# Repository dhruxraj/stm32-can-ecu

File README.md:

# STM32 CAN ECU – development board (rev A)

A compact, "ECU-style" CAN node for learning and prototyping automotive-type embedded software. It has an STM32G4 MCU, a CAN transceiver with protection and switchable termination, a 6-axis IMU, a protected 8-18 V supply, SWD, a UART, LEDs and buttons.

Two or more identical boards talk to each other over CANH/CANL/GND. Each board broadcasts:

* a heartbeat,
* IMU data,
* supply voltage,
* diagnostics.

Each board also supervises its peers.

## Quick facts

| | |
|---|---|
| MCU | **STM32G431CBT6** (Cortex-M4F 170 MHz, 128 KB flash, 32 KB RAM, LQFP48) |
| CAN transceiver | **NXP TJA1051T/3** (5 V VCC, 3.3 V VIO), PESD1CAN ESD, split termination on jumper |
| IMU | **ST LSM6DS3TR-C** (accel ±4 g, gyro ±500 dps, I2C 0x6A) |
| Supply | **8-18 V DC** (12 V nominal): PTC + TVS + reverse-polarity diode → RECOM R-78E5.0-0.5 (5 V) → AP2112K-3.3 LDO |
| Power | ≈ 0.35 W typical, < 0.85 W worst case (≈ 28 mA typical / 67 mA worst case at 12 V) |
| PCB | **80 × 60 mm, 4 layers** (signal / GND / 3V3 / signal), 1.6 mm, 4 × M3 |
| CAN | classic CAN 500 kbit/s, 11-bit IDs, counter + CRC-8 on every frame |
| Est. BOM cost | ≈ USD 19 components per board (qty 10, rough estimate) + PCB |
| Tools | KiCad 7/8/9, STM32CubeIDE or CMake + arm-none-eabi-gcc, ST-LINK |

## Repository layout

```
README.md                  this file
docs/                      all documentation (start with BRINGUP.md when your boards arrive)
hardware/kicad/            KiCad project: CAN_ECU.kicad_pro / .kicad_sch / .kicad_pcb + libraries
hardware/fab/              preview Gerbers, drill files, BOM.csv, CPL_top.csv
hardware/gen/              Python generators + independent checkers (how rev A was produced)
firmware/                  STM32Cube HAL firmware (CMake / CubeIDE), host unit tests
tools/                     can_ecu.dbc, Python decoder/monitor (python-can)
```

## Architecture

| Document | Content |
|---|---|
| [docs/DESIGN_NOTES.md](docs/DESIGN_NOTES.md) | architecture, all design decisions, circuit calculations, **assumptions list**, limitations, future work |
| [docs/POWER_CALCS.md](docs/POWER_CALCS.md) | per-rail current budget, regulator dissipation, input current, total power |
| [docs/PIN_MAPPING.md](docs/PIN_MAPPING.md) | all 48 MCU pins, alternate functions, connector and jumper pinouts |
| [docs/COMPONENTS.md](docs/COMPONENTS.md) | component list and footprint list (with **VERIFY** notes) |
| [docs/PCB_LAYOUT.md](docs/PCB_LAYOUT.md) | stack-up, rules, placement and routing strategy |
| [docs/CAN_PROTOCOL.md](docs/CAN_PROTOCOL.md) | IDs, byte layouts, scaling, rates, status bits, counter/CRC, fault bits |
| [docs/FIRMWARE.md](docs/FIRMWARE.md) | module structure, scheduler, robustness features, building, programming |
| [docs/MANUFACTURING.md](docs/MANUFACTURING.md) | fab spec, how to produce/order Gerbers, assembly notes, cost |
| [docs/BRINGUP.md](docs/BRINGUP.md) | step-by-step bring-up, **two-board CAN test**, troubleshooting |
| [docs/TEST_CHECKLIST.md](docs/TEST_CHECKLIST.md) | per-board test sheet |
| [docs/VALIDATION_REPORT.md](docs/VALIDATION_REPORT.md) | results of all automated checks and what could not be checked |

## Hardware overview

* **Power input.** J1 (5.08 mm screw terminal) → F1 PTC 0.5 A → D1 SMBJ18A TVS → D2 SS34 series Schottky → 10 µF + 47 µF → R-78E 5 V module → AP2112K 3.3 V LDO. The MCU's analog supply (VDDA/VREF+) is filtered by FB1. The PWR LED is on +5 V. VIN is measured by the MCU (PA0).
* **MCU.** STM32G431CBT6 with an 8 MHz crystal (PLL 170 MHz) and 100 nF per VDD pin plus 4.7 µF bulk. It has a reset button and SWD header, BOOT0 pull-down plus jumper, and two node-ID jumpers. Unused pins are left unconnected and set to analog.
* **CAN.** FDCAN1 (PA11/PA12) → TJA1051T/3 → PESD1CAN → J2/J3 (1 CANH, 2 CANL, 3 GND, paralleled). JP2 enables the 2 × 60.4 Ω split termination with 4.7 nF to GND. The transceiver's S pin holds it silent until the firmware is ready. Test pads: TP1 CANH, TP2 CANL, TP7 CAN_TX, TP8 CAN_RX.
* **IMU.** LSM6DS3TR-C on I2C1 (PA15/PB7, 4k7 pull-ups), with INT1/INT2 wired to PB5/PB9.
* **User interface.** LEDs STATUS/FAULT/CAN-TX/CAN-RX plus PWR; RESET and USER buttons; J5 2×5 header (3.3 V UART + 5 GPIO/ADC).

## Software overview

* **Firmware.** Bare-metal C using the STM32Cube HAL. A cooperative scheduler runs 10/20/100/1000 ms tasks.
* **CAN.** Interrupt-driven FDCAN RX into a ring buffer, with hardware ID filters and automatic bus-off recovery.
* **Protocol.** IMU data at 50 Hz, heartbeat and board data at 10 Hz, diagnostics at 1 Hz. Every frame carries a rolling counter and a CRC-8.
* **Supervision.** Peer heartbeat timeout of 300 ms. Node states are INIT/RUN/DEGRADED/FAULT, with 13 fault bits (active + latched).
* **Robustness.** Independent watchdog (~1 s), reset-cause reporting, crystal-failure fallback, IMU fault detection with auto re-init.
* **PC side.** `tools/can_monitor.py` (python-can) decodes and verifies all frames and can send commands. `tools/can_ecu.dbc` works in any CAN analyzer.

## Getting started

### 1. Open the design in KiCad

1. Install KiCad 7, 8 or 9.
2. Copy/unzip the project and open **`hardware/kicad/CAN_ECU.kicad_pro`**.
   * Symbols and footprints come from the project-local libraries `CAN_ECU.kicad_sym` / `CAN_ECU.pretty`. They are registered in the project's `sym-lib-table` / `fp-lib-table`, so no library setup is needed.
   * KiCad 8/9 will say the files were made by an older version. Accept; saving converts them.
3. **Schematic:** open the schematic editor and run **Inspect → Electrical Rules Checker**.
4. **PCB:**
   1. Open the PCB editor and press **B** (Fill All Zones). The planes and pours are stored unfilled.
   2. Run **Inspect → Design Rules Checker**. Enable "Test for parity between PCB and schematic".
   3. Use **View → 3D Viewer** for a sanity check. 3D models are not linked, so only footprint outlines appear.

### 2. Order boards

See [docs/MANUFACTURING.md](docs/MANUFACTURING.md). In short:

1. Fill the zones, run DRC and plot Gerbers + drill files from KiCad.
2. Order a 4-layer, 1.6 mm board with ENIG finish.
3. Buy the parts from `hardware/fab/BOM.csv`. Verify the footprints marked **VERIFY** in docs/COMPONENTS.md first.

### 3. Build and flash the firmware

```bash
cd firmware && ./scripts/fetch_st_drivers.sh
cmake -B build -DCMAKE_TOOLCHAIN_FILE=cmake/gcc-arm-none-eabi.cmake && cmake --build build
STM32_Programmer_CLI -c port=SWD mode=UR -w build/can_ecu.hex -v -rst
```

Connect the ST-LINK to J4:

| J4 pin | Signal |
|---|---|
| 1 | VDD (sense) |
| 2 | SWCLK |
| 3 | GND |
| 4 | SWDIO |
| 5 | NRST |
| 6 | SWO |

The board must be powered from J1 while you program it. For the console, use a 3.3 V USB-UART on J5 (pin 3 TX, pin 4 RX, pin 2 GND) at 115200 8N1. CubeIDE instructions are in [docs/FIRMWARE.md](docs/FIRMWARE.md).

### 4. Connect two boards and test CAN

1. Board A: JP3 and JP4 open (**node 0**). Board B: **JP3 closed (node 1)**.
2. On a 2-node bus both boards are bus ends, so **fit both JP2 shunts (1-3 and 2-4) on both boards**. With power off, CANH-CANL must measure ≈ 60 Ω.
3. Wire J2/J3 pin 1-1 (CANH), 2-2 (CANL), 3-3 (GND), using a twisted pair for CANH/CANL.
4. Power both boards (8-18 V).
5. Check the result:
   * Both STATUS LEDs flash at 1 Hz (RUN) and the CAN-TX/RX LEDs flicker.
   * Each UART prints `peer node X online`, and the status line shows the peer's accelerometer values.
   * Pressing USER on one board makes the other blink fast for 3 s.
   * Unplugging the cable gives `PEER_TIMEOUT` (DEGRADED) within 300 ms; the boards recover automatically when you plug it back in.
6. With a USB-CAN adapter, run `python3 tools/can_monitor.py -i socketcan -c can0`. Expect about 121 frames/s per node with zero CRC or counter errors.

The full procedure, expected values and scope checks are in [docs/BRINGUP.md](docs/BRINGUP.md).

## Troubleshooting (short)

| Symptom | Check |
|---|---|
| One board alone shows DEGRADED + `CAN_PASSIVE` | Normal: CAN needs a second node to acknowledge frames. |
| Two boards don't see each other | Node IDs must differ. Check CANH↔CANH / CANL↔CANL wiring, the GND wire, and that termination measures ≈ 60 Ω. |
| `HSI16 FALLBACK` printed | Crystal not starting: check the joints and C16/C17. |
| `IMU_COMM` fault / WHO_AM_I 0x00 | IMU (LGA) soldering, or pull-ups R13/R14. |
| No +3V3 | U2 orientation; a short on +3V3. |
| ST-LINK can't connect | Use "connect under reset"; make sure JP1 (BOOT0) is open. |

More in [docs/BRINGUP.md](docs/BRINGUP.md#5-troubleshooting).

## Validation status (honest summary)

* **PCB design-rule check** (independent checker, 0.2 mm rules): **0 violations, 0 unconnected nets**. Both planes are continuous, and there are no courtyard overlaps.
* **Generated KiCad files re-parsed:**
  * S-expression syntax is valid.
  * The schematic netlist equals the PCB netlist for all 46 nets.
  * The ERC subset passes, and there are no silkscreen collisions.
* **Firmware:** 60 host unit checks pass (protocol, diagnostics, IMU conversion). All sources compile cleanly against a HAL stub, and the Python decoder matches the C golden frames.
* **Not verified here:**
  * KiCad's own ERC/DRC and zone fill (KiCad was not available).
  * A real arm-none-eabi build against the ST HAL.
  * Operation on hardware.
  * Footprints marked VERIFY.

  Details and remaining risks are in [docs/VALIDATION_REPORT.md](docs/VALIDATION_REPORT.md) and [docs/DESIGN_NOTES.md](docs/DESIGN_NOTES.md#4-assumptions-and-items-that-were-not-fully-verified).

## Limitations

This is a development board, **not an automotive-qualified ECU**:

* No ISO 7637 / ISO 16750 load-dump protection.
* No CAN common-mode choke.
* No USB in rev A: it conflicts with the CAN pins on this MCU.
* A single CAN channel.
* The counter/CRC/state machine is AUTOSAR-*inspired*, not compliant.

See [docs/DESIGN_NOTES.md](docs/DESIGN_NOTES.md#5-limitations-of-rev-a).

## Future improvements

* A 2-FDCAN MCU with USB-C.
* A discrete wide-input buck with ideal-diode reverse protection and load-dump rating.
* CAN FD, and a CAN bootloader.
* A CMC footprint.
* UDS-style diagnostics.

See [docs/DESIGN_NOTES.md](docs/DESIGN_NOTES.md#6-future-improvements).

## License

This project uses separate licenses for hardware, software, and documentation.

- **Hardware:** CERN-OHL-P-2.0
- **Firmware and software tools:** MIT License
- **Documentation:** CC BY 4.0

See the corresponding `LICENSE-*` files in the repository for the
complete license terms.

Third-party components retain their original licenses.

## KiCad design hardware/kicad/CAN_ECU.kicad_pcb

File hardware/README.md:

# Hardware

```
hardware/
  kicad/     KiCad project (open CAN_ECU.kicad_pro) + project symbol/footprint libraries
  fab/       preview Gerbers, drill files, BOM.csv, CPL_top.csv (regenerate from KiCad for ordering)
  gen/       Python generators - the design "source code"
```

`gen/` is how every hardware file in this project was produced. KiCad itself was not available while the files were generated, so they were written by these scripts.

| Script | Purpose |
|---|---|
| `design.py` | parts, values, part numbers and the pin→net netlist (single source of truth) |
| `lib.py` | symbol and footprint definitions |
| `board.py` | board outline and component placement |
| `routing.py` | hand routes, plane fan-out and a constrained router for the low-speed nets |
| `write_kicad.py` | writes the `.kicad_sch/.kicad_pcb/.kicad_pro/.kicad_sym/.pretty` files |
| `checks.py` | independent DRC, connectivity and plane-continuity checks |
| `validate_files.py` | re-parses the written files: syntax, schematic↔PCB netlist, ERC subset, silkscreen |
| `fab.py` | Gerber/Excellon/BOM/CPL + Gerber re-render |
| `gen_docs.py` | pin map, component list, validation report, figures |

Regenerate everything (Python 3.10+, numpy, scipy, matplotlib): `cd hardware/gen && ./build_all.sh`

**Recommended workflow once you own the design:** open the project in KiCad and continue there. KiCad becomes the source of truth from that point, and the generators are then only a record of how rev A was made. Do not mix the two workflows: re-running the generators overwrites manual KiCad edits.

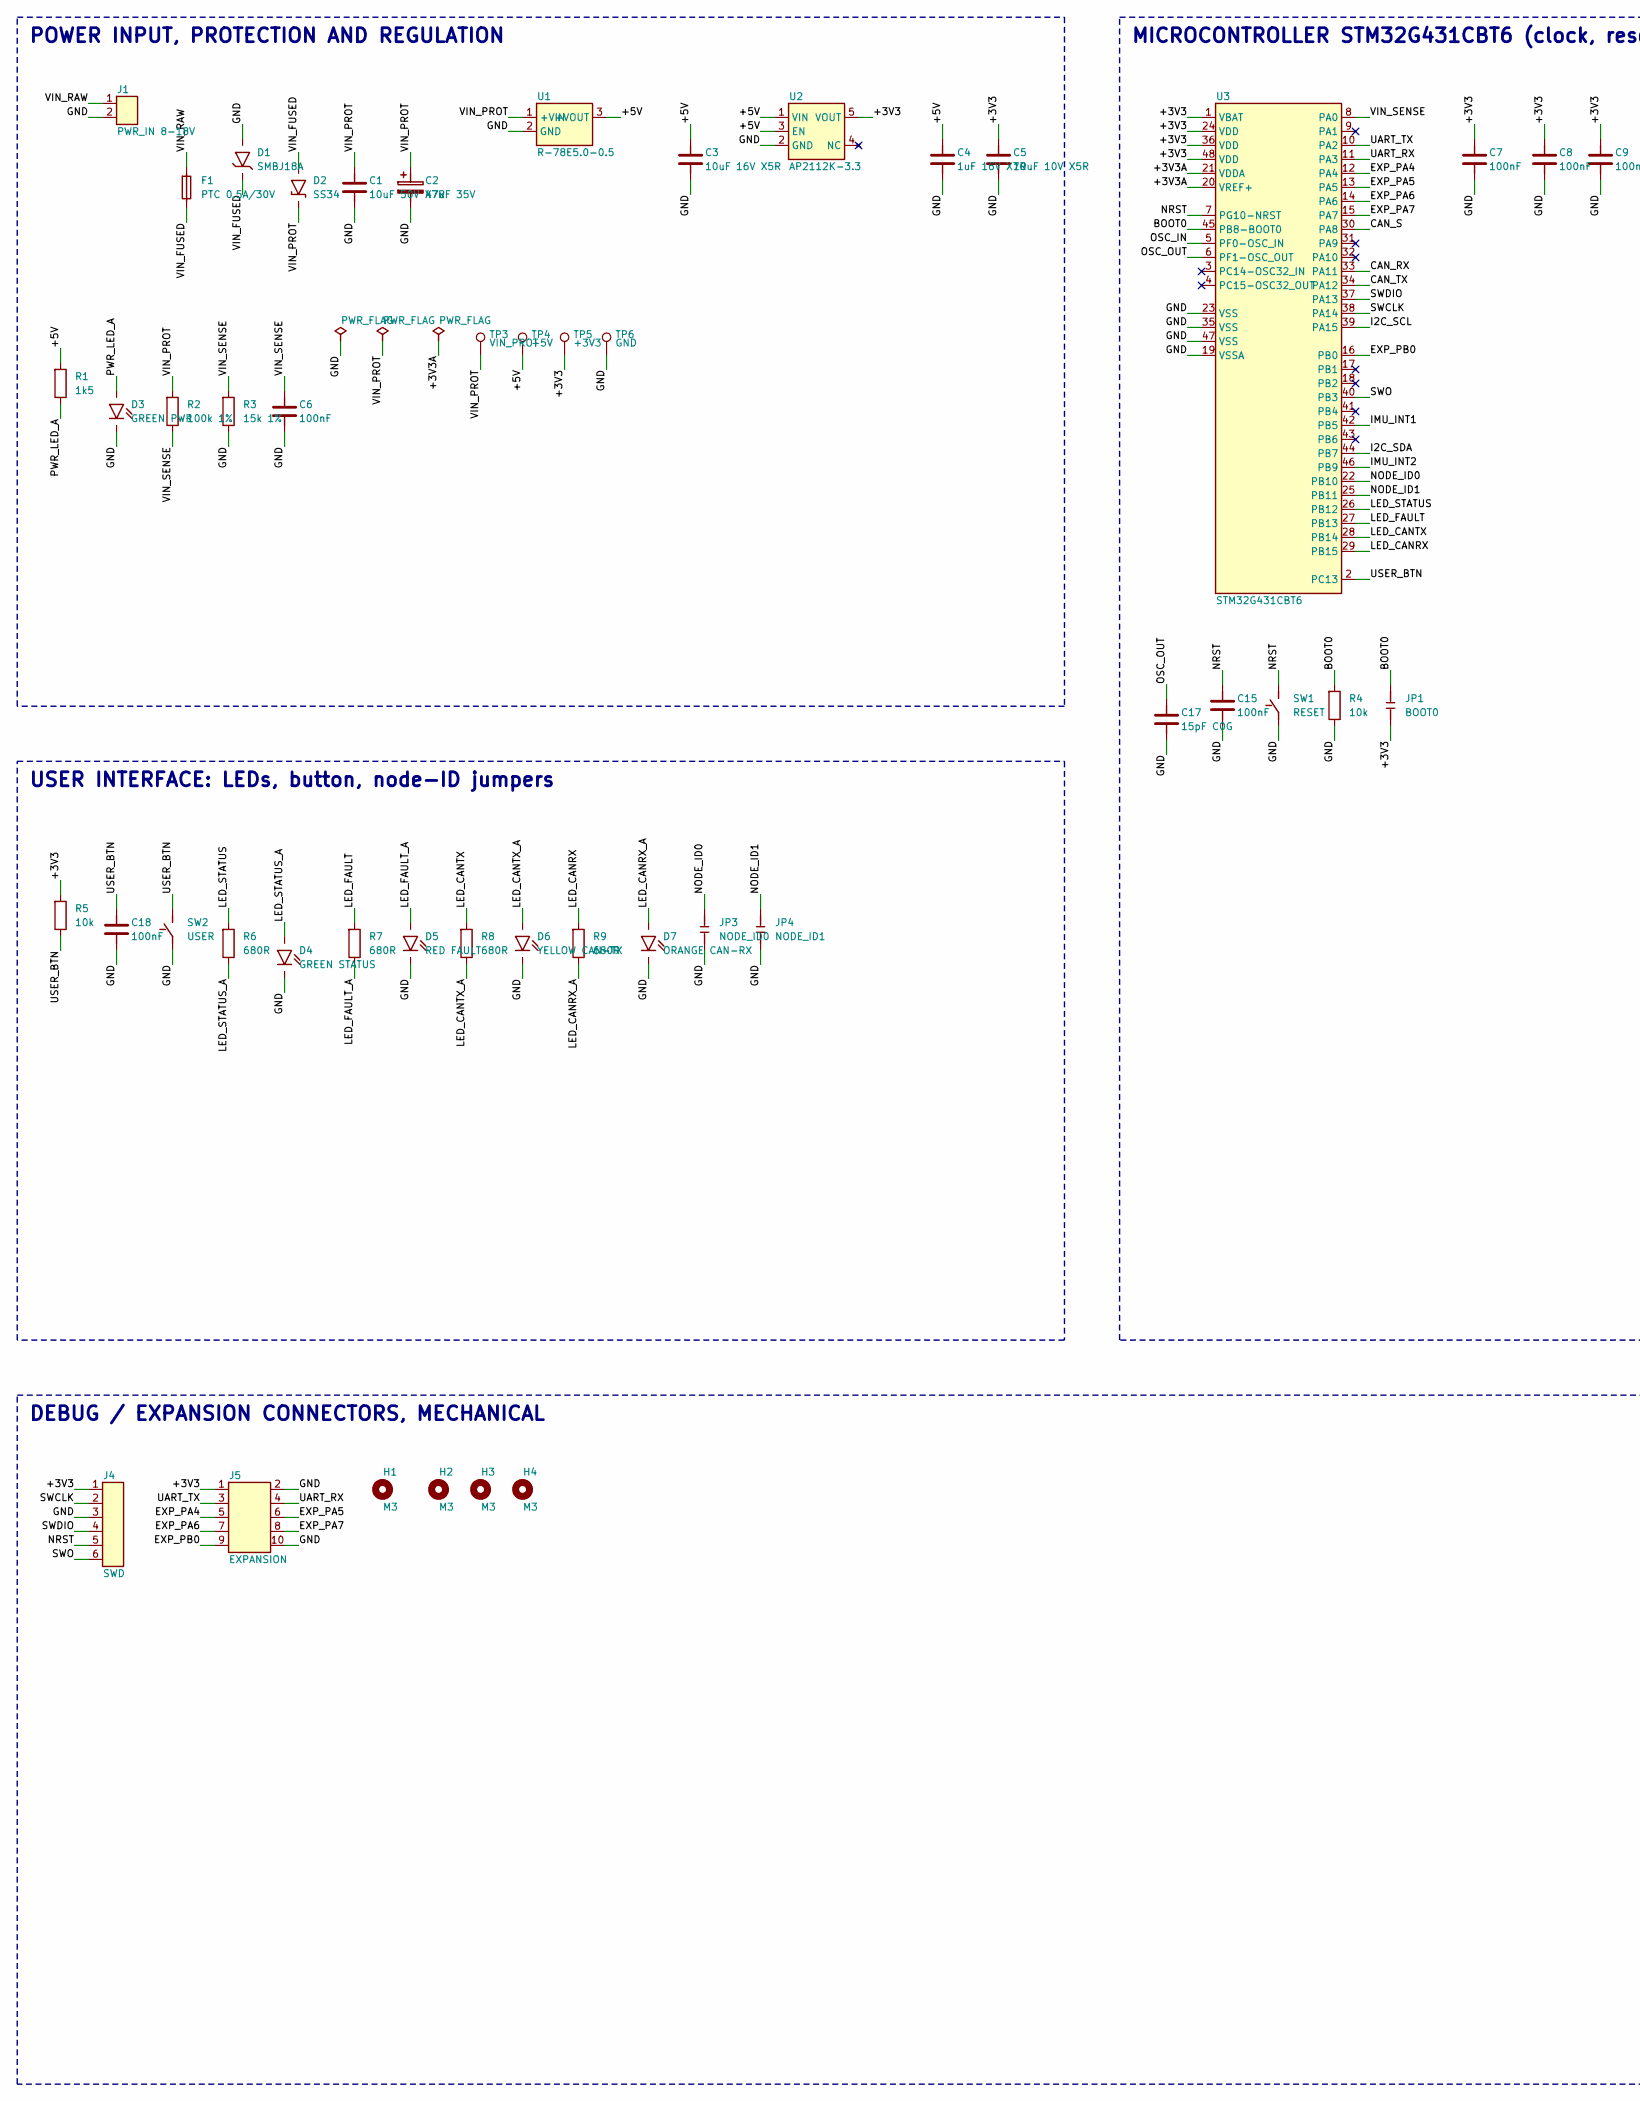
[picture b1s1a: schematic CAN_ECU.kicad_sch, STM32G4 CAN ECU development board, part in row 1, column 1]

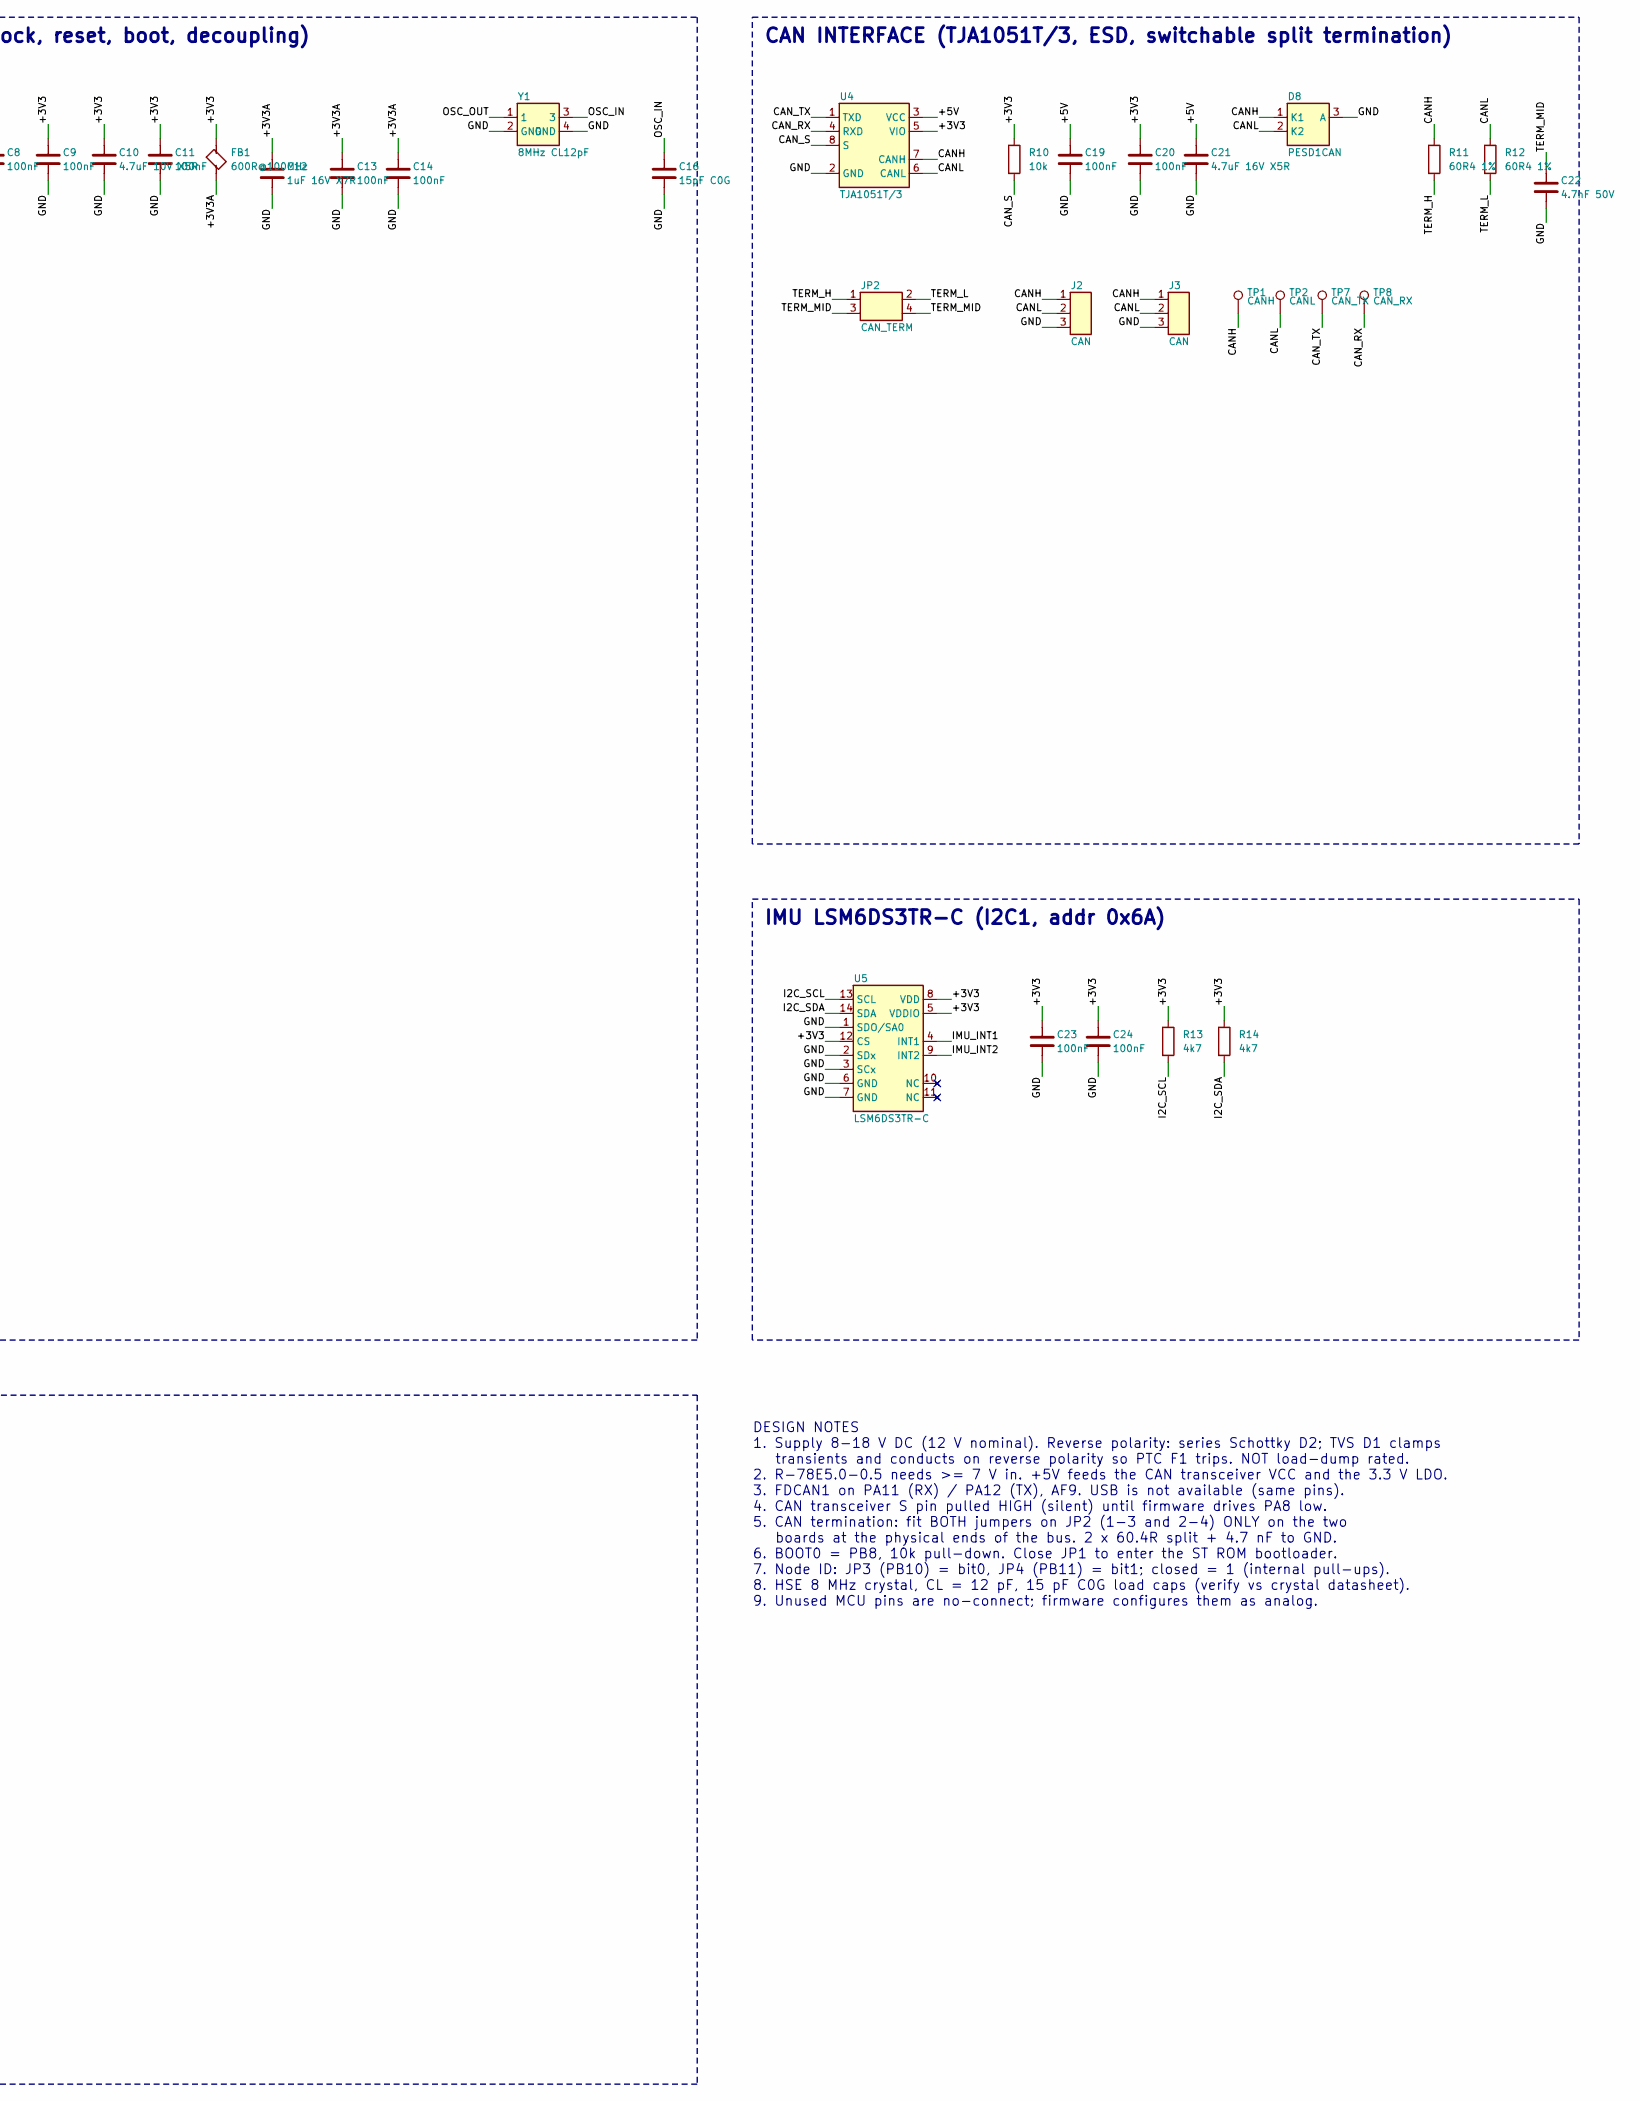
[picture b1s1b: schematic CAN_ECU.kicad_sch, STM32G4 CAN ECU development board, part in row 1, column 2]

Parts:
C1: 10uF 50V X7R; C_1210_3225Metric
C2: 47uF 35V; CP_Radial_D6.3mm_P2.50mm; MPN 47 uF 35 V aluminium electrolytic, D6.3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
C3: 10uF 16V X5R; C_0805_2012Metric
C4, C12: 1uF 16V X7R; C_0603_1608Metric
C5: 10uF 10V X5R; C_0805_2012Metric
C6, C7, C8, C9, C11, C13, C14, C15, C18, C19, C20, C23, C24: 100nF; C_0603_1608Metric
C10: 4.7uF 10V X5R; C_0805_2012Metric
C16, C17: 15pF C0G; C_0603_1608Metric
C21: 4.7uF 16V X5R; C_0805_2012Metric
C22: 4.7nF 50V; C_0603_1608Metric
D1: SMBJ18A; D_SMB; MPN SMBJ18A
D2: SS34; D_SMA; MPN SS34
D3: GREEN PWR; LED_0603_1608Metric; MPN 0603 green LED, Vf~2.0 V
D4: GREEN STATUS; LED_0603_1608Metric; MPN 0603 green LED
D5: RED FAULT; LED_0603_1608Metric; MPN 0603 red LED
D6: YELLOW CAN-TX; LED_0603_1608Metric; MPN 0603 yellow LED
D7: ORANGE CAN-RX; LED_0603_1608Metric; MPN 0603 orange LED
D8: PESD1CAN; SOT-23; MPN PESD1CAN,215
F1: PTC 0.5A/30V; Fuse_1812_4532Metric; MPN 1812 PTC, Ihold 0.5 A, Vmax >= 30 V (e.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
FB1: 600R@100MHz; L_0603_1608Metric; MPN BLM18AG601SN1D (or equiv. 0603 bead, >=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
H1, H2, H3, H4: M3; MountingHole_3.2mm_M3
J1: PWR_IN 8-18V; TerminalBlock_1x02_P5.08mm_Horizontal; MPN 1729128 (MKDS 1,5/ 2-5,08) or equivalent
J2, J3: CAN; TerminalBlock_1x03_P5.08mm_Horizontal; MPN 1729131 (MKDS 1,5/ 3-5,08) or equivalent
J4: SWD; PinHeader_1x06_P2.54mm_Vertical; MPN 1x6 2.54 mm pin header
J5: EXPANSION; PinHeader_2x05_P2.54mm_Vertical; MPN 2x5 2.54 mm pin header
JP1: BOOT0; SolderJumper-2_P1.3mm_Open_Pad1.0x1.5mm
JP2: CAN_TERM; PinHeader_2x02_P2.54mm_Vertical; MPN 2x2 2.54 mm header + 2 jumper shunts
JP3: NODE_ID0; SolderJumper-2_P1.3mm_Open_Pad1.0x1.5mm
JP4: NODE_ID1; SolderJumper-2_P1.3mm_Open_Pad1.0x1.5mm
R1: 1k5; R_0603_1608Metric
R2: 100k 1%; R_0603_1608Metric
R3: 15k 1%; R_0603_1608Metric
R4, R5, R10: 10k; R_0603_1608Metric
R6, R7, R8, R9: 680R; R_0603_1608Metric
R11, R12: 60R4 1%; R_0805_2012Metric
R13, R14: 4k7; R_0603_1608Metric
SW1: RESET; SW_PUSH_6mm; MPN 6x6 mm THT tactile switch
SW2: USER; SW_PUSH_6mm; MPN 6x6 mm THT tactile switch
TP1: CANH; TestPoint_Pad_D1.5mm
TP2: CANL; TestPoint_Pad_D1.5mm
TP3: VIN_PROT; TestPoint_Pad_D1.5mm
TP4: +5V; TestPoint_Pad_D1.5mm
TP5: +3V3; TestPoint_Pad_D1.5mm
TP6: GND; TestPoint_Pad_D1.5mm
TP7: CAN_TX; TestPoint_Pad_D1.5mm
TP8: CAN_RX; TestPoint_Pad_D1.5mm
U1: R-78E5.0-0.5; Converter_DCDC_RECOM_R-78E-0.5_THT; MPN R-78E5.0-0.5
U2: AP2112K-3.3; SOT-23-5; MPN AP2112K-3.3TRG1
U3: STM32G431CBT6; LQFP-48_7x7mm_P0.5mm; MPN STM32G431CBT6
U4: TJA1051T/3; SOIC-8_3.9x4.9mm_P1.27mm; MPN TJA1051T/3,118
U5: LSM6DS3TR-C; LGA-14_3x2.5mm_P0.5mm_LayoutBorder3x4y; MPN LSM6DS3TR-C
Y1: 8MHz CL12pF; Crystal_SMD_3225-4Pin_3.2x2.5mm; MPN 8.000 MHz, 3225 4-pad, +-20 ppm, CL = 1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

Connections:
+3V3: C5.1, C7.1, C8.1, C9.1, C10.1, C11.1, C20.1, C23.1, C24.1, FB1.1, J4.1, J5.1, JP1.2, R5.1, R10.1, R13.1, R14.1, TP5.1, U2.5 (VOUT), U3.1 (VBAT), U3.24 (VDD), U3.36 (VDD), U3.48 (VDD), U4.5 (VIO), U5.5 (VDDIO), U5.8 (VDD), U5.12 (CS)
+3V3A: C12.1, C13.1, C14.1, FB1.2, U3.20 (VREF+), U3.21 (VDDA)
+5V: C3.1, C4.1, C19.1, C21.1, R1.1, TP4.1, U1.3 (+VOUT), U2.1 (VIN), U2.3 (EN), U4.3 (VCC)
BOOT0: JP1.1, R4.1, U3.45 (PB8-BOOT0)
CANH: D8.1 (K1), J2.1, J3.1, R11.1, TP1.1, U4.7 (CANH)
CANL: D8.2 (K2), J2.2, J3.2, R12.1, TP2.1, U4.6 (CANL)
CAN_RX: TP8.1, U3.33 (PA11), U4.4 (RXD)
CAN_S: R10.2, U3.30 (PA8), U4.8 (S)
CAN_TX: TP7.1, U3.34 (PA12), U4.1 (TXD)
EXP_PA4: J5.5, U3.12 (PA4)
EXP_PA5: J5.6, U3.13 (PA5)
EXP_PA6: J5.7, U3.14 (PA6)
EXP_PA7: J5.8, U3.15 (PA7)
EXP_PB0: J5.9, U3.16 (PB0)
GND: C1.2, C2.2, C3.2, C4.2, C5.2, C6.2, C7.2, C8.2, C9.2, C10.2, C11.2, C12.2, C13.2, C14.2, C15.2, C16.2, C17.2, C18.2, C19.2, C20.2, C21.2, C22.2, C23.2, C24.2, D1.2 (A), D3.1 (K), D4.1 (K), D5.1 (K), D6.1 (K), D7.1 (K), D8.3 (A), J1.2, J2.3, J3.3, J4.3, J5.2, J5.10, JP3.2, JP4.2, R3.2, R4.2, SW1.2, SW2.2, TP6.1, U1.2 (GND), U2.2 (GND), U3.19 (VSSA), U3.23 (VSS), U3.35 (VSS), U3.47 (VSS), U4.2 (GND), U5.1 (SDO/SA0), U5.2 (SDx), U5.3 (SCx), U5.6 (GND), U5.7 (GND), Y1.2 (GND), Y1.4 (GND)
I2C_SCL: R13.2, U3.39 (PA15), U5.13 (SCL)
I2C_SDA: R14.2, U3.44 (PB7), U5.14 (SDA)
IMU_INT1: U3.42 (PB5), U5.4 (INT1)
IMU_INT2: U3.46 (PB9), U5.9 (INT2)
LED_CANRX: R9.1, U3.29 (PB15)
LED_CANRX_A: D7.2 (A), R9.2
LED_CANTX: R8.1, U3.28 (PB14)
LED_CANTX_A: D6.2 (A), R8.2
LED_FAULT: R7.1, U3.27 (PB13)
LED_FAULT_A: D5.2 (A), R7.2
LED_STATUS: R6.1, U3.26 (PB12)
LED_STATUS_A: D4.2 (A), R6.2
NODE_ID0: JP3.1, U3.22 (PB10)
NODE_ID1: JP4.1, U3.25 (PB11)
NRST: C15.1, J4.5, SW1.1, U3.7 (PG10-NRST)
OSC_IN: C16.1, U3.5 (PF0-OSC_IN), Y1.3
OSC_OUT: C17.1, U3.6 (PF1-OSC_OUT), Y1.1
PWR_LED_A: D3.2 (A), R1.2
SWCLK: J4.2, U3.38 (PA14)
SWDIO: J4.4, U3.37 (PA13)
SWO: J4.6, U3.40 (PB3)
TERM_H: JP2.1, R11.2
TERM_L: JP2.2, R12.2
TERM_MID: C22.1, JP2.3, JP2.4
UART_RX: J5.4, U3.11 (PA3)
UART_TX: J5.3, U3.10 (PA2)
USER_BTN: C18.1, R5.2, SW2.1, U3.2 (PC13)
VIN_FUSED: D1.1 (K), D2.2 (A), F1.2
VIN_PROT: C1.1, C2.1, D2.1 (K), R2.1, TP3.1, U1.1 (+VIN)
VIN_RAW: F1.1, J1.1
VIN_SENSE: C6.1, R2.2, R3.1, U3.8 (PA0)

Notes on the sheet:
POWER INPUT, PROTECTION AND REGULATION
MICROCONTROLLER STM32G431CBT6 (clock, reset, boot, decoupling)
CAN INTERFACE (TJA1051T/3, ESD, switchable split termination)
IMU LSM6DS3TR-C (I2C1, addr 0x6A)
USER INTERFACE: LEDs, button, node-ID jumpers
DEBUG / EXPANSION CONNECTORS, MECHANICAL
DESIGN NOTES 1. Supply 8-18 V DC (12 V nominal). Reverse polarity: series Schottky D2; TVS D1 clamps transients and conducts on reverse polarity so PTC F1 trips. NOT load-dump rated. 2. R-78E5.0-0.5 needs >= 7 V in. +5V feeds the CAN transceiver VCC and the 3.3 V LDO. 3. FDCAN1 on PA11 (RX) / PA12 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

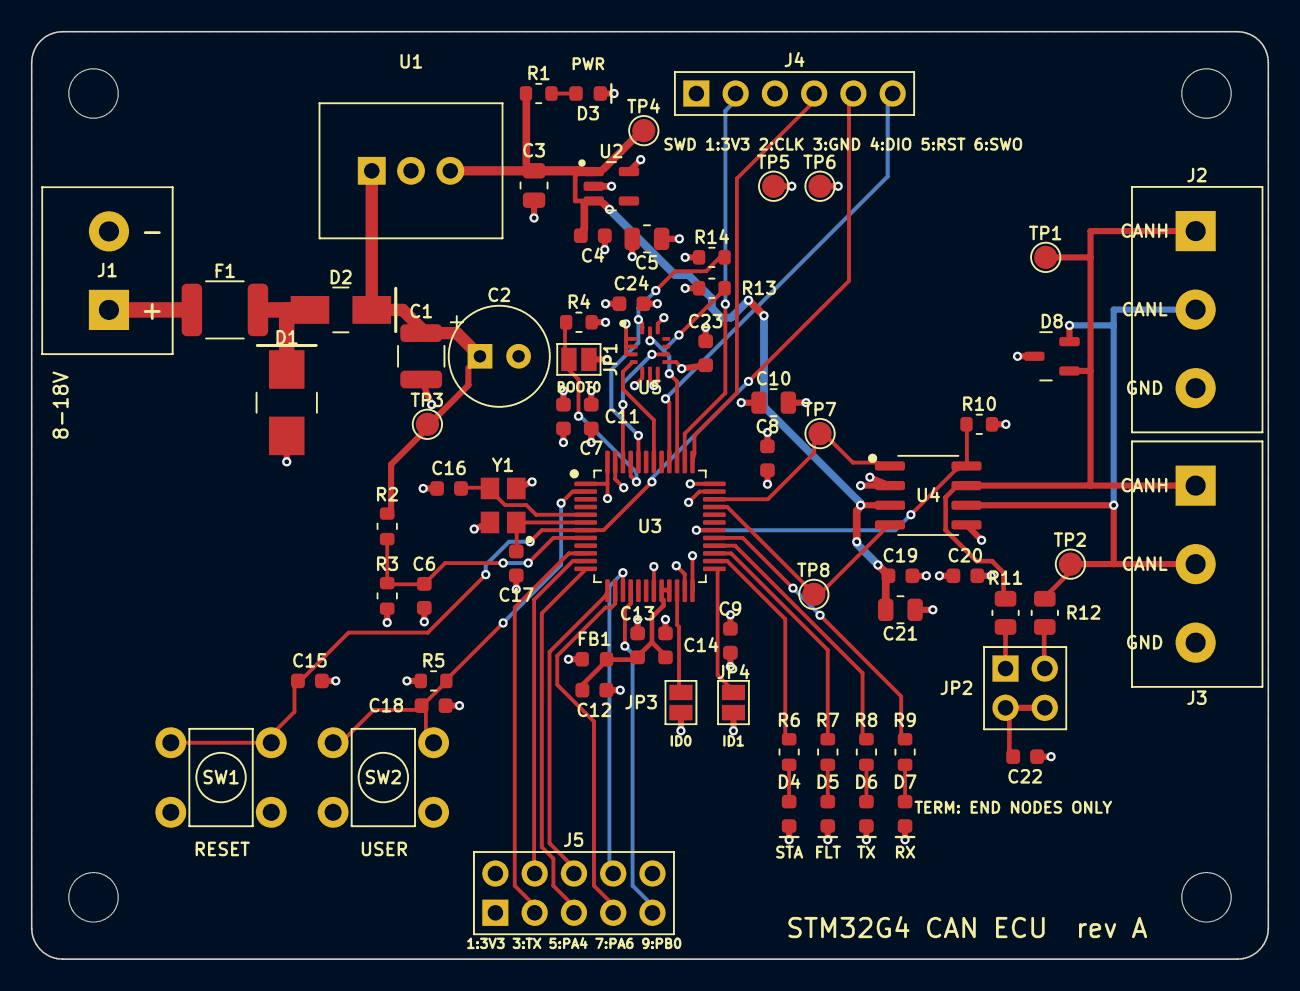
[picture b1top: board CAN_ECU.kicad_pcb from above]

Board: 4 copper layers, 80.0 x 60.0 mm, 77 parts (0 on the bottom side), 46 nets.

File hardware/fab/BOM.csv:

Item,Qty,References,Value,Footprint (project lib),Equivalent KiCad std footprint,MPN / specification,Manufacturer,Description,Mount,Est. unit USD,Est. ext. USD
1,1,C1,10uF 50V X7R,C_1210_3225Metric,Capacitor_SMD:C_1210_3225Metric,"generic 10uF 50V X7R, 1210",any,Input ceramic 10 uF 50 V X7R 1210,SMD,0.35,0.35
2,1,C2,47uF 35V,CP_Radial_D6.3mm_P2.50mm,Capacitor_THT:CP_Radial_D6.3mm_P2.50mm,"47 uF 35 V aluminium electrolytic, D6.3 mm, P2.5 mm, low-ESR",any,Input bulk / damping capacitor,THT,0.20,0.20
3,1,C3,10uF 16V X5R,C_0805_2012Metric,Capacitor_SMD:C_0805_2012Metric,"generic 10uF 16V X5R, 0805",any,5 V rail output capacitor 0805,SMD,0.08,0.08
4,2,C4 C12,1uF 16V X7R,C_0603_1608Metric,Capacitor_SMD:C_0603_1608Metric,"generic 1uF 16V X7R, 0603",any,LDO input capacitor; VDDA bulk,SMD,0.03,0.06
5,1,C5,10uF 10V X5R,C_0805_2012Metric,Capacitor_SMD:C_0805_2012Metric,"generic 10uF 10V X5R, 0805",any,LDO output capacitor,SMD,0.08,0.08
6,13,C6 C7 C8 C9 C11 C13 C14 C15 C18 C19 C20 C23 C24,100nF,C_0603_1608Metric,Capacitor_SMD:C_0603_1608Metric,"generic 100nF, 0603",any,"Ceramic capacitor 100nF, 0603; IMU VDD decoupling; IMU VDDIO decoupling; NRST filter; Transceiver VCC decoupling; Transceiver VIO decoupling; User button debounce; VBAT decoupling; VDD pin 24 decoupling; VDD pin 36 decoupling; VDD pin 48 decoupling; VDDA decoupling; VREF+ decoupling",SMD,0.02,0.26
7,1,C10,4.7uF 10V X5R,C_0805_2012Metric,Capacitor_SMD:C_0805_2012Metric,"generic 4.7uF 10V X5R, 0805",any,VDD bulk,SMD,0.06,0.06
8,2,C16 C17,15pF C0G,C_0603_1608Metric,Capacitor_SMD:C_0603_1608Metric,"generic 15pF C0G, 0603",any,HSE load cap (for CL = 12 pF crystal),SMD,0.03,0.06
9,1,C21,4.7uF 16V X5R,C_0805_2012Metric,Capacitor_SMD:C_0805_2012Metric,"generic 4.7uF 16V X5R, 0805",any,Transceiver VCC bulk,SMD,0.06,0.06
10,1,C22,4.7nF 50V,C_0603_1608Metric,Capacitor_SMD:C_0603_1608Metric,"generic 4.7nF 50V, 0603",any,Split termination common-mode capacitor,SMD,0.03,0.03
11,1,D1,SMBJ18A,D_SMB,Diode_SMD:D_SMB,SMBJ18A,Littelfuse,"600 W unidirectional TVS, VRWM 18 V, SMB",SMD,0.25,0.25
12,1,D2,SS34,D_SMA,Diode_SMD:D_SMA,SS34,onsemi/various,"3 A 40 V Schottky, reverse-polarity protection, SMA",SMD,0.15,0.15
13,1,D3,GREEN PWR,LED_0603_1608Metric,LED_SMD:LED_0603_1608Metric,"0603 green LED, Vf~2.0 V",any,Power indicator (5 V rail),SMD,0.05,0.05
14,1,D4,GREEN STATUS,LED_0603_1608Metric,LED_SMD:LED_0603_1608Metric,0603 green LED,any,STATUS indicator,SMD,0.05,0.05
15,1,D5,RED FAULT,LED_0603_1608Metric,LED_SMD:LED_0603_1608Metric,0603 red LED,any,FAULT indicator,SMD,0.05,0.05
16,1,D6,YELLOW CAN-TX,LED_0603_1608Metric,LED_SMD:LED_0603_1608Metric,0603 yellow LED,any,CAN-TX indicator,SMD,0.05,0.05
17,1,D7,ORANGE CAN-RX,LED_0603_1608Metric,LED_SMD:LED_0603_1608Metric,0603 orange LED,any,CAN-RX indicator,SMD,0.05,0.05
18,1,D8,PESD1CAN,SOT-23,Package_TO_SOT_SMD:SOT-23,"PESD1CAN,215",Nexperia,"CAN bus ESD protection, SOT-23 (verify pinout: 1,2 = bus lines, 3 = GND)",SMD,0.25,0.25
19,1,F1,PTC 0.5A/30V,Fuse_1812_4532Metric,Fuse:Fuse_1812_4532Metric,"1812 PTC, Ihold 0.5 A, Vmax >= 30 V (e.g. Bourns MF-MSMF series - select 30 V rated)",Bourns/Littelfuse,"Resettable PTC fuse, 1812",SMD,0.35,0.35
20,1,FB1,600R@100MHz,L_0603_1608Metric,Inductor_SMD:L_0603_1608Metric,"BLM18AG601SN1D (or equiv. 0603 bead, >=200 mA)",Murata,VDDA filter bead,SMD,0.05,0.05
21,1,J1,PWR_IN 8-18V,TerminalBlock_1x02_P5.08mm_Horizontal,"TerminalBlock_Phoenix:TerminalBlock_Phoenix_MKDS-1,5-2-5.08_1x02_P5.08mm_Horizontal","1729128 (MKDS 1,5/ 2-5,08) or equivalent",Phoenix Contact,"2-pos 5.08 mm PCB screw terminal, power input (1 = +VIN, 2 = GND)",THT,0.70,0.70
22,2,J2 J3,CAN,TerminalBlock_1x03_P5.08mm_Horizontal,"TerminalBlock_Phoenix:TerminalBlock_Phoenix_MKDS-1,5-3-5.08_1x03_P5.08mm_Horizontal","1729131 (MKDS 1,5/ 3-5,08) or equivalent",Phoenix Contact,"CAN bus connector (1 = CANH, 2 = CANL, 3 = GND); J2/J3 are paralleled for daisy-chain",THT,1.00,2.00
23,1,J4,SWD,PinHeader_1x06_P2.54mm_Vertical,Connector_PinHeader_2.54mm:PinHeader_1x06_P2.54mm_Vertical,1x6 2.54 mm pin header,any,"SWD: 1 VDD_TARGET, 2 SWCLK, 3 GND, 4 SWDIO, 5 NRST, 6 SWO (Nucleo CN4 order)",THT,0.25,0.25
24,1,J5,EXPANSION,PinHeader_2x05_P2.54mm_Vertical,Connector_PinHeader_2.54mm:PinHeader_2x05_P2.54mm_Vertical,2x5 2.54 mm pin header,any,Expansion / debug UART (USART2),THT,0.35,0.35
25,1,JP2,CAN_TERM,PinHeader_2x02_P2.54mm_Vertical,Connector_PinHeader_2.54mm:PinHeader_2x02_P2.54mm_Vertical,2x2 2.54 mm header + 2 jumper shunts,any,Termination enable: fit BOTH shunts (1-3 and 2-4) on end-of-bus nodes only,THT,0.30,0.30
26,1,R1,1k5,R_0603_1608Metric,Resistor_SMD:R_0603_1608Metric,"generic 1k5, 0603",any,"Resistor 1k5, 0603, 1%, thick film",SMD,0.01,0.01
27,1,R2,100k 1%,R_0603_1608Metric,Resistor_SMD:R_0603_1608Metric,"generic 100k 1%, 0603",any,"VIN divider top, 1%",SMD,0.01,0.01
28,1,R3,15k 1%,R_0603_1608Metric,Resistor_SMD:R_0603_1608Metric,"generic 15k 1%, 0603",any,"VIN divider bottom, 1%",SMD,0.01,0.01
29,3,R4 R5 R10,10k,R_0603_1608Metric,Resistor_SMD:R_0603_1608Metric,"generic 10k, 0603",any,BOOT0 pull-down (boot from Flash); Transceiver S pull-up: SILENT until firmware enables; User button pull-up,SMD,0.01,0.03
30,4,R6 R7 R8 R9,680R,R_0603_1608Metric,Resistor_SMD:R_0603_1608Metric,"generic 680R, 0603",any,"Resistor 680R, 0603, 1%, thick film",SMD,0.01,0.04
31,2,R11 R12,60R4 1%,R_0805_2012Metric,Resistor_SMD:R_0805_2012Metric,"generic 60R4 1%, 0805",any,Split termination 60.4R 0805,SMD,0.04,0.08
32,2,R13 R14,4k7,R_0603_1608Metric,Resistor_SMD:R_0603_1608Metric,"generic 4k7, 0603",any,I2C SCL pull-up; I2C SDA pull-up,SMD,0.01,0.02
33,1,SW1,RESET,SW_PUSH_6mm,Button_Switch_THT:SW_PUSH_6mm,6x6 mm THT tactile switch,any,Reset push-button,THT,0.15,0.15
34,1,SW2,USER,SW_PUSH_6mm,Button_Switch_THT:SW_PUSH_6mm,6x6 mm THT tactile switch,any,User push-button,THT,0.15,0.15
35,1,U1,R-78E5.0-0.5,Converter_DCDC_RECOM_R-78E-0.5_THT,Converter_DCDC:Converter_DCDC_RECOM_R-78E-0.5_THT,R-78E5.0-0.5,RECOM,"5 V 0.5 A non-isolated switching regulator module, 7-28 V in, SIP-3",THT,3.60,3.60
36,1,U2,AP2112K-3.3,SOT-23-5,Package_TO_SOT_SMD:SOT-23-5,AP2112K-3.3TRG1,Diodes Inc.,"3.3 V 600 mA LDO, SOT-23-5",SMD,0.35,0.35
37,1,U3,STM32G431CBT6,LQFP-48_7x7mm_P0.5mm,Package_QFP:LQFP-48_7x7mm_P0.5mm,STM32G431CBT6,STMicroelectronics,"Cortex-M4F 170 MHz, 128 KB Flash, 32 KB RAM, FDCAN, LQFP48",SMD,4.60,4.60
38,1,U4,TJA1051T/3,SOIC-8_3.9x4.9mm_P1.27mm,Package_SO:SOIC-8_3.9x4.9mm_P1.27mm,"TJA1051T/3,118",NXP,"High-speed CAN (FD) transceiver with VIO, SO8. Must be the /3 (VIO) variant!",SMD,1.10,1.10
39,1,U5,LSM6DS3TR-C,LGA-14_3x2.5mm_P0.5mm_LayoutBorder3x4y,Package_LGA:LGA-14_3x2.5mm_P0.5mm_LayoutBorder3x4y,LSM6DS3TR-C,STMicroelectronics,"6-axis IMU (accel + gyro), I2C addr 0x6A",SMD,2.40,2.40
40,1,Y1,8MHz CL12pF,Crystal_SMD_3225-4Pin_3.2x2.5mm,Crystal:Crystal_SMD_3225-4Pin_3.2x2.5mm,"8.000 MHz, 3225 4-pad, +-20 ppm, CL = 12 pF (ESR <= 100R)",any,HSE crystal for accurate CAN bit timing,SMD,0.40,0.40

,,,,,,,,"Estimated component total per board (qty-10 pricing, ROUGH ESTIMATE - check distributor)",,,19.09
,,JP1 JP3 JP4,Solder jumpers,,,PCB feature - no part,,,,,
,,TP1-TP8,Test pads,,,PCB feature - no part,,,,,
,,H1-H4,M3 mounting holes,,,PCB feature - no part,,,,,

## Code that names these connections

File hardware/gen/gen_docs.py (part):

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FPS = build_footprints()

MCU_FUNC = {
    "PC13": "USER button SW2 (active low, ext. 10k pull-up)", "PF0-OSC_IN": "HSE 8 MHz crystal Y1",
    "PF1-OSC_OUT": "HSE 8 MHz crystal Y1", "PG10-NRST": "Reset: SW1, C15 100 nF, SWD pin 5",
    "PA0": "ADC1_IN1 - VIN sense divider 100k/15k", "PA2": "USART2_TX (AF7) debug console -> J5.3",
    "PA3": "USART2_RX (AF7) debug console -> J5.4", "PA4": "Expansion J5.5 (GPIO/ADC/DAC)",
    "PA5": "Expansion J5.6", "PA6": "Expansion J5.7", "PA7": "Expansion J5.8", "PB0": "Expansion J5.9",
    "PB10": "NODE_ID bit0 - solder jumper JP3 to GND (internal pull-up)",
    "PB11": "NODE_ID bit1 - solder jumper JP4 to GND (internal pull-up)",
    "PB12": "LED STATUS (green) via 680R", "PB13": "LED FAULT (red) via 680R",
    "PB14": "LED CAN-TX (yellow) via 680R", "PB15": "LED CAN-RX (orange) via 680R",
    "PA8": "CAN transceiver S (silent) - 10k pull-up, LOW = normal",
    "PA11": "FDCAN1_RX (AF9) <- TJA1051 RXD", "PA12": "FDCAN1_TX (AF9) -> TJA1051 TXD",
    "PA13": "SWDIO (J4.4)", "PA14": "SWCLK (J4.2)", "PA15": "I2C1_SCL (AF4) - IMU, 4k7 pull-up",
    "PB3": "SWO trace output (J4.6)", "PB5": "IMU INT1 (accel data-ready)", "PB7": "I2C1_SDA (AF4) - IMU, 4k7 pull-up",
    "PB8-BOOT0": "BOOT0: 10k pull-down, JP1 to 3V3 = system bootloader", "PB9": "IMU INT2 (spare)",
    "VBAT": "+3V3 (no backup battery), 100 nF", "VDD": "+3V3, 100 nF per pin + 4.7 uF bulk",
    "VSS": "GND", "VSSA": "GND", "VDDA": "+3V3A (ferrite FB1 + 1 uF + 100 nF)", "VREF+": "+3V3A, 100 nF",
}
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        L.append(f"| {n} | {nm} | {net or '-'} | {func} |")
    L += ["", "## Alternate-function summary", "",
          "| Peripheral | Signal | Pin | AF |", "|---|---|---|---|",
          "| FDCAN1 | RX | PA11 | AF9 |", "| FDCAN1 | TX | PA12 | AF9 |",
          "| I2C1 | SCL | PA15 | AF4 |", "| I2C1 | SDA | PB7 | AF4 |",
          "| USART2 | TX | PA2 | AF7 |", "| USART2 | RX | PA3 | AF7 |",
          "| SWD | SWDIO / SWCLK / SWO | PA13 / PA14 / PB3 | AF0 (reset default) |",
          "| ADC1 | IN1 (VIN sense) | PA0 | analog |", "",
          "**Why no USB:** on the STM32G431 the only FDCAN1 pin pair that does not collide with other "
          "functions here is PA11/PA12 - the same pins as USB DM/DP. The alternative FDCAN1 pins PB8/PB9 "
          "would put CAN RX on the BOOT0 pin (PB8), which is a known source of boot problems. Rev A therefore "
          "uses PA11/PA12 for CAN and provides a 3.3 V UART on J5 instead of USB.", ""]
    L += ["## Connectors", ""]
    for ref, title in [("J1", "Power input (5.08 mm screw terminal)"), ("J2", "CAN bus A (5.08 mm, 3-pole)"),
                       ("J3", "CAN bus B (5.08 mm, 3-pole, parallel to J2 for daisy-chaining)"),
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    L += ["## Jumpers", "", "| Ref | Function | Open (default) | Closed |", "|---|---|---|---|",
          "| JP1 | BOOT0 | boot from flash | ST system bootloader (UART/FDCAN/I2C/SPI) |",
          "| JP2 | CAN termination (2 shunts) | no termination | 2 x 60.4 R split + 4.7 nF |",
          "| JP3 | NODE_ID bit 0 (PB10) | 0 | 1 |", "| JP4 | NODE_ID bit 1 (PB11) | 0 | 1 |", "",
          "Node ID = JP4*2 + JP3 -> 0..3. Two boards must have **different** node IDs "
          "(e.g. board A: both open = node 0; board B: JP3 closed = node 1).", ""]
    open(os.path.join(DOCS, "PIN_MAPPING.md"), "w").write("\n".join(L))
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    "SOIC-8_3.9x4.9mm_P1.27mm": "Standard JEDEC MS-012 land pattern.",
    "Converter_DCDC_RECOM_R-78E-0.5_THT": "**VERIFY** pin pitch (2.54 mm) and body side against the RECOM drawing; 6.5 mm keep-out reserved both sides.",
    "Crystal_SMD_3225-4Pin_3.2x2.5mm": "Standard 3225 4-pad; confirm pad 1/3 = crystal, 2/4 = GND for the chosen part.",
    "SOT-23": "**VERIFY** PESD1CAN pinout (1 = CANH/line, 2 = CANL/line, 3 = common) - symmetric part, swapping 1/2 is harmless.",
    "SOT-23-5": "AP2112K SOT-23-5 pinout checked (1 VIN, 2 GND, 3 EN, 4 NC, 5 VOUT).",
    "TerminalBlock_1x02_P5.08mm_Horizontal": "**VERIFY** hole size/pitch vs. the terminal block actually bought (Phoenix MKDS 1,5/2-5,08 style).",
    "TerminalBlock_1x03_P5.08mm_Horizontal": "**VERIFY** as above (3-pole).",
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
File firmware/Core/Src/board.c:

/**
 * @file    board.c
 * @brief   GPIO configuration, LEDs, button, node ID, ADC measurements.
 */
#include "board.h"

ADC_HandleTypeDef hadc1;

static const struct { GPIO_TypeDef *port; uint16_t pin; } s_led[LED_COUNT] = {
    { LED_STATUS_PORT, LED_STATUS_PIN }, { LED_FAULT_PORT, LED_FAULT_PIN },
    { LED_CANTX_PORT, LED_CANTX_PIN },   { LED_CANRX_PORT, LED_CANRX_PIN },
};

void board_gpio_init(void)
{
    GPIO_InitTypeDef g = {0};
    __HAL_RCC_GPIOA_CLK_ENABLE();
    __HAL_RCC_GPIOB_CLK_ENABLE();
    __HAL_RCC_GPIOC_CLK_ENABLE();
    __HAL_RCC_GPIOF_CLK_ENABLE();

    /* outputs: safe levels first */
    HAL_GPIO_WritePin(GPIOB, LED_STATUS_PIN | LED_FAULT_PIN | LED_CANTX_PIN | LED_CANRX_PIN, GPIO_PIN_RESET);
    HAL_GPIO_WritePin(CAN_S_PORT, CAN_S_PIN, GPIO_PIN_SET);          /* transceiver silent */

    g.Pin = LED_STATUS_PIN | LED_FAULT_PIN | LED_CANTX_PIN | LED_CANRX_PIN;
    g.Mode = GPIO_MODE_OUTPUT_PP;
    g.Pull = GPIO_NOPULL;
    g.Speed = GPIO_SPEED_FREQ_LOW;
    HAL_GPIO_Init(GPIOB, &g);

    g.Pin = CAN_S_PIN;
    HAL_GPIO_Init(CAN_S_PORT, &g);

    g.Pin = BTN_USER_PIN;
    g.Mode = GPIO_MODE_INPUT;
    g.Pull = GPIO_NOPULL;                                             /* external 10k */
    HAL_GPIO_Init(BTN_USER_PORT, &g);

    g.Pin = NODE_ID0_PIN | NODE_ID1_PIN;
    g.Pull = GPIO_PULLUP;
    HAL_GPIO_Init(GPIOB, &g);

    g.Pin = IMU_INT1_PIN | IMU_INT2_PIN;
    g.Pull = GPIO_PULLDOWN;                                           /* IMU INT is push-pull */
    HAL_GPIO_Init(GPIOB, &g);

    /* unused / not-connected pins -> analog (lowest power, no floating inputs).
     * Expansion header pins PA4..PA7, PB0 are also left analog until used.   */
    g.Mode = GPIO_MODE_ANALOG;
    g.Pull = GPIO_NOPULL;
    g.Pin = GPIO_PIN_1 | GPIO_PIN_4 | GPIO_PIN_5 | GPIO_PIN_6 | GPIO_PIN_7 | GPIO_PIN_9 | GPIO_PIN_10;
    HAL_GPIO_Init(GPIOA, &g);
    g.Pin = GPIO_PIN_0 | GPIO_PIN_1 | GPIO_PIN_2 | GPIO_PIN_4 | GPIO_PIN_6;
    HAL_GPIO_Init(GPIOB, &g);
    g.Pin = GPIO_PIN_14 | GPIO_PIN_15;
    HAL_GPIO_Init(GPIOC, &g);
}

void board_led(led_t led, bool on)
{
    if (led < LED_COUNT) {
        HAL_GPIO_WritePin(s_led[led].port, s_led[led].pin, on ? GPIO_PIN_SET : GPIO_PIN_RESET);
    }
}

bool board_button_pressed(void)
{
    return HAL_GPIO_ReadPin(BTN_USER_PORT, BTN_USER_PIN) == GPIO_PIN_RESET;
}

uint8_t board_node_id(void)
{
    uint8_t id = 0;
    if (HAL_GPIO_ReadPin(NODE_ID0_PORT, NODE_ID0_PIN) == GPIO_PIN_RESET) id |= 1u;
    if (HAL_GPIO_ReadPin(NODE_ID1_PORT, NODE_ID1_PIN) == GPIO_PIN_RESET) id |= 2u;
    return id;
}

void board_can_transceiver_normal(bool normal)
{
    HAL_GPIO_WritePin(CAN_S_PORT, CAN_S_PIN, normal ? GPIO_PIN_RESET : GPIO_PIN_SET);
}

/* ------------------------------------------------------------------ ADC */
bool board_adc_init(void)
{
    hadc1.Instance = ADC1;
    hadc1.Init.ClockPrescaler = ADC_CLOCK_SYNC_PCLK_DIV4;     /* 170/4 = 42.5 MHz */
    hadc1.Init.Resolution = ADC_RESOLUTION_12B;
    hadc1.Init.DataAlign = ADC_DATAALIGN_RIGHT;
    hadc1.Init.GainCompensation = 0;
    hadc1.Init.ScanConvMode = ADC_SCAN_DISABLE;
    hadc1.Init.EOCSelection = ADC_EOC_SINGLE_CONV;
    hadc1.Init.LowPowerAutoWait = DISABLE;
    hadc1.Init.ContinuousConvMode = DISABLE;
    hadc1.Init.NbrOfConversion = 1;
    hadc1.Init.DiscontinuousConvMode = DISABLE;
    hadc1.Init.ExternalTrigConv = ADC_SOFTWARE_START;
    hadc1.Init.ExternalTrigConvEdge = ADC_EXTERNALTRIGCONVEDGE_NONE;
    hadc1.Init.DMAContinuousRequests = DISABLE;
    hadc1.Init.Overrun = ADC_OVR_DATA_OVERWRITTEN;
    hadc1.Init.OversamplingMode = DISABLE;
    if (HAL_ADC_Init(&hadc1) != HAL_OK) {
        return false;
    }
    return HAL_ADCEx_Calibration_Start(&hadc1, ADC_SINGLE_ENDED) == HAL_OK;
}

static bool adc_read(uint32_t channel, uint32_t *raw)
{
    ADC_ChannelConfTypeDef c = {0};
    c.Channel = channel;
    c.Rank = ADC_REGULAR_RANK_1;
    c.SamplingTime = ADC_SAMPLETIME_247CYCLES_5;              /* >5 us for VREFINT/TS */
    c.SingleDiff = ADC_SINGLE_ENDED;
    c.OffsetNumber = ADC_OFFSET_NONE;
    c.Offset = 0;
    if (HAL_ADC_ConfigChannel(&hadc1, &c) != HAL_OK) return false;
    if (HAL_ADC_Start(&hadc1) != HAL_OK) return false;
    if (HAL_ADC_PollForConversion(&hadc1, 2) != HAL_OK) {
        (void)HAL_ADC_Stop(&hadc1);
        return false;
    }
    *raw = HAL_ADC_GetValue(&hadc1);
    (void)HAL_ADC_Stop(&hadc1);
    return true;
}

static uint32_t vdda_mv(void)
{
    uint32_t vref = 0;
    if (!adc_read(ADC_CHANNEL_VREFINT, &vref) || vref == 0u) {
        return 3300u;                                       /* nominal fallback */
    }
    return __HAL_ADC_CALC_VREFANALOG_VOLTAGE(vref, ADC_RESOLUTION_12B);
}

uint16_t board_vin_mv(void)
{
    uint32_t raw = 0;
    uint32_t vdda = vdda_mv();
    if (!adc_read(ADC_CHANNEL_1, &raw)) {
        return 0u;
    }
    uint32_t pin_mv = (raw * vdda) / 4095u;
    return (uint16_t)((pin_mv * VIN_DIV_NUM) / VIN_DIV_DEN);
}

int16_t board_mcu_temp_c(void)
{
    uint32_t raw = 0;
    uint32_t vdda = vdda_mv();
    if (!adc_read(ADC_CHANNEL_TEMPSENSOR_ADC1, &raw)) {
        return INT16_MIN;
    }
    return (int16_t)__HAL_ADC_CALC_TEMPERATURE(vdda, raw, ADC_RESOLUTION_12B);
}
